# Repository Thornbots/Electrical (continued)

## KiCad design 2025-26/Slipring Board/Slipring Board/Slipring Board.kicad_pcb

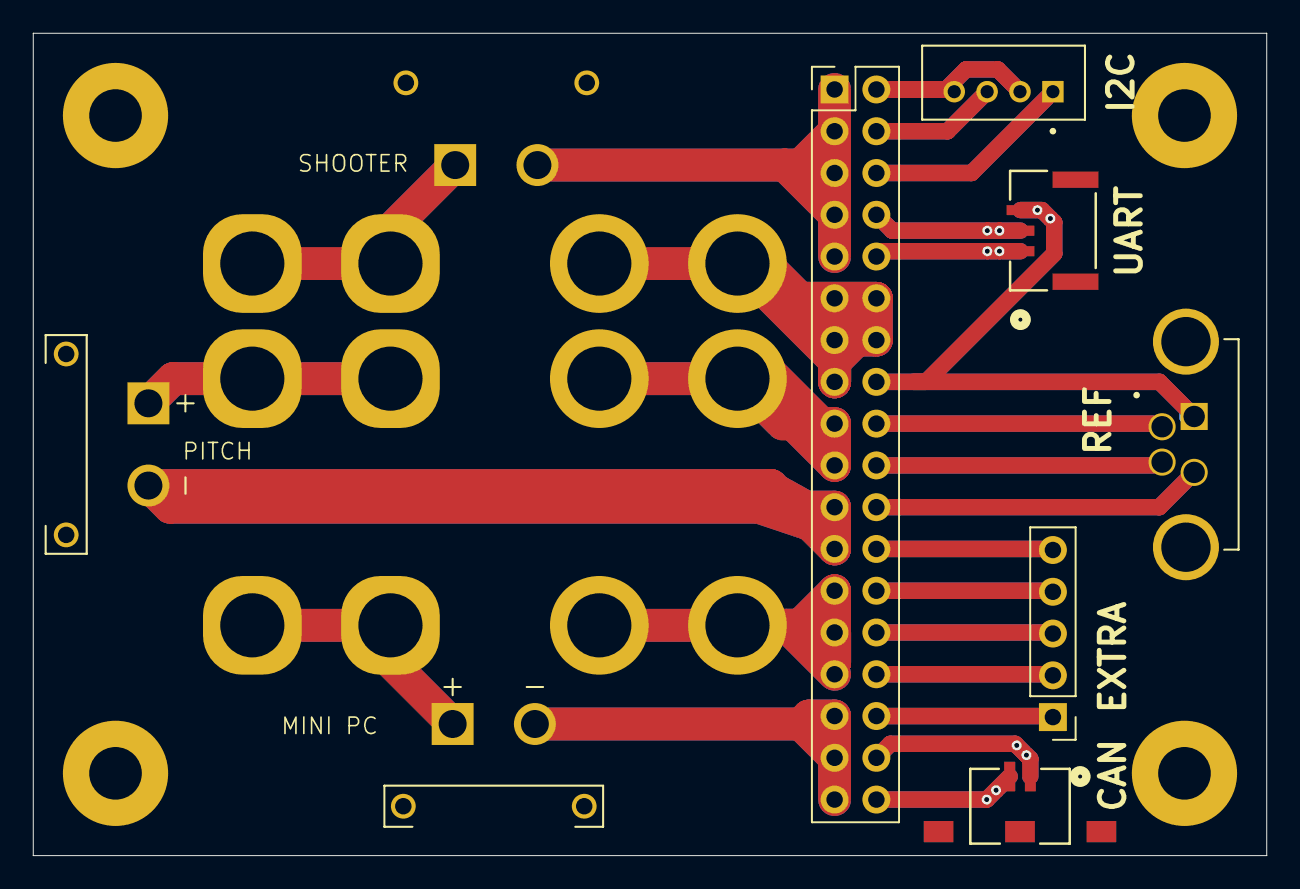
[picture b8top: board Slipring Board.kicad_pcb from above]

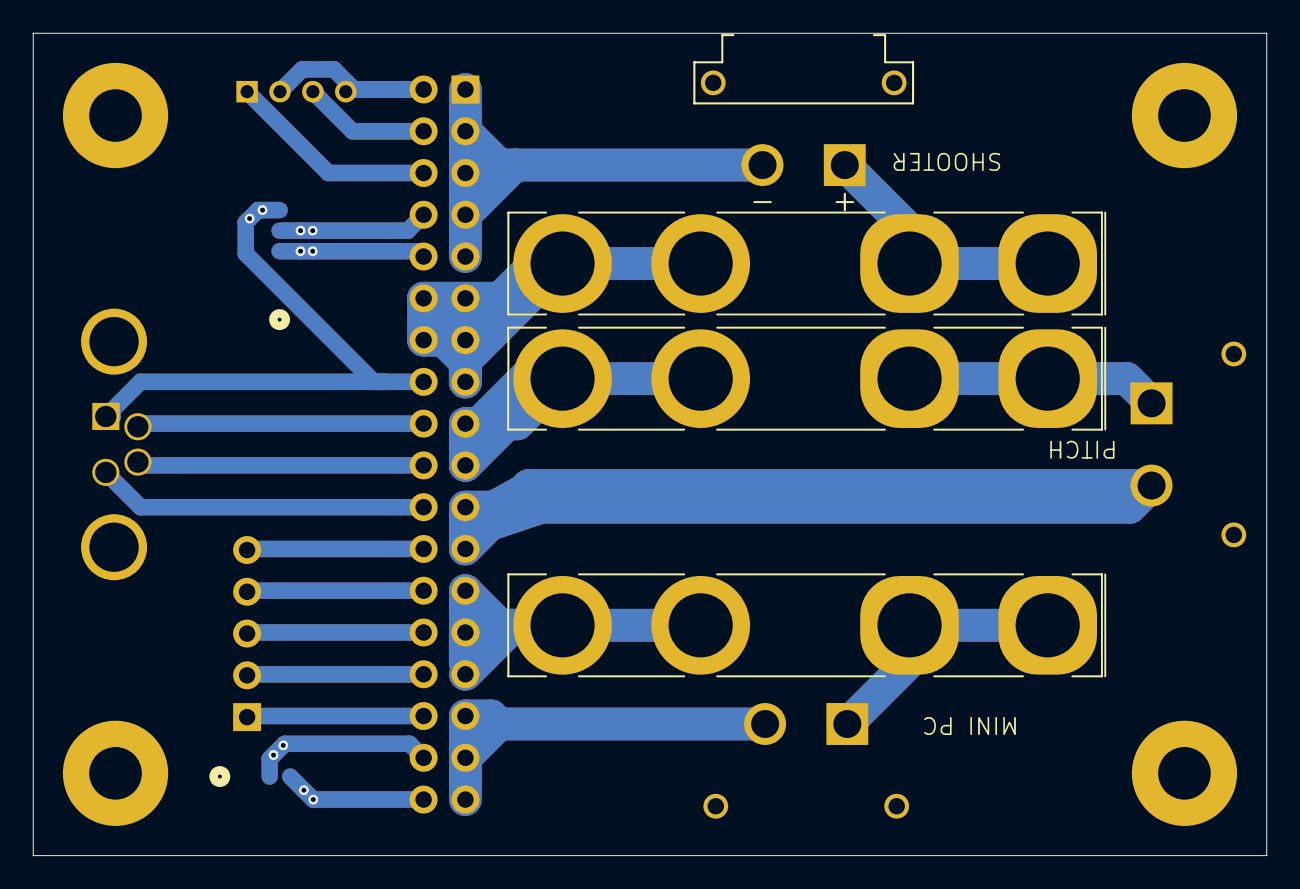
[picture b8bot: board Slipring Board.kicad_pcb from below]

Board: 2 copper layers, 75.0 x 50.0 mm, 12 parts (4 on the bottom side), 25 nets.

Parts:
F1, F2, F3: Fuse; Fuseholder_Keystone_3555-2
J1, J2, J3: Conn_01x02; AMASS_XT30PW-F
J4: JST GH 2pin; CONN_BM02B-GHS-TBT_JST
J5: M8 Aviator; AMPHENOL_M8S-04PFFR-SF8001
J6: JST GH 3pin; CONN_BM03B-GHS-TBT_JST
J7: JST PH 4pin; JST_B4B-PH-K
J8: Conn_02x18_Odd_Even; PinHeader_2x18_P2.54mm_Vertical
J9: Conn_01x05_Pin; PinHeader_1x05_P2.54mm_Vertical

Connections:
/CAN High: J4.2, J8.36
/CAN Low: J4.1, J8.34
/I2C Clock: J7.1, J8.6
/I2C Data: J7.3, J8.4
/I2C GND: J7.2, J7.4, J8.2
/Mini PC +24: F3.1, J3.1
/Mini PC GND: J3.2, J8.31, J8.33, J8.35
/Pitch +24: F2.1, J2.1
/Pitch GND: J2.2, J8.21, J8.23
/REF / UART GND: J5.1, J6.3, J8.16
/Ref +: J5.2, J8.18
/Ref Data A: J5.4, J8.20
/Ref Data B: J5.3, J8.22
/Shooter +24V: F1.1, J1.1
/Shooter GND: J1.2, J8.1, J8.3, J8.5, J8.7, J8.9
/UART 1 rx: J6.2, J8.8
/UART 1 tx: J6.1, J8.10
unnamed: F1.2, J8.11, J8.12, J8.13, J8.14, J8.15
unnamed: F2.2, J8.17, J8.19
unnamed: J8.24, J9.5
unnamed: F3.2, J8.25, J8.27, J8.29
unnamed: J8.26, J9.4
unnamed: J8.28, J9.3
unnamed: J8.30, J9.2
unnamed: J8.32, J9.1

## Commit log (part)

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2023-09-06 Create Lila Beghtel
2023-09-09 example project 1
2023-09-10 initial project commit
2023-09-10 power planes NOW
2023-09-10 project 1 mcdaniel
2023-09-10 project1
2023-09-10 Project 1 (Battershell_Luci)
2023-09-10 meeting 1
2023-09-10 groovy
2023-09-10 its not a bomb I promise
    its not a bomb I promise
2023-09-10 Practice
2023-09-10 bonillml-project-1
2023-09-10 prj1
2023-09-10 project2
2023-09-17 still not a bomb
2023-09-26 USBC Thingy
2023-09-26 aaaaa
2023-09-26 project 1
2023-09-26 power first push
2023-09-26 Boinkers (CAN)
2023-09-26 sd card reader first push
2023-09-26 Create RP2040
2023-09-26 new folder stuff
2023-09-30 found part
2023-10-01 rp2040 progress
2023-10-01 rp2040 update
2023-10-01 GPIO / UART
2023-10-01 2040 update
2023-10-01 done
2023-10-01 not important
2023-10-01 nothing important
2023-10-01 some power stuff variables
2023-10-01 I want to scream
2023-10-01 Added subschematic box
2023-10-01 fixed some minor wiring
2023-10-01 hmmm
2023-10-01 GPIO
2023-10-01 My Attempt at a CAN bus SPI bridge
2023-10-01 commented on evan's thing
2023-10-03 Fixed my schematic
2023-10-03 GPIO, USBC
2023-10-03 CAN booos
2023-10-07 power powered
2023-10-10 pushing origin
2023-10-10 fixed ben's whoopsie
2023-10-10 Fixed
2023-10-10 making heirachical sheet thing and switching docs
    changing to RP2040ACTUAL03 and 04 cuz it disappeared ?
2023-10-10 Changed Global to Hierarchals
2023-10-10 extra naming stuff
2023-10-10 We went thru eveeeryyything
2023-10-10 Idk what changed here
2023-10-10 GP1O to GPIO :|
2023-10-10 Found a symbol for the SD card reader
2023-10-10 Moved symbol to box
2023-10-10 Put SD Card Reader in box and added to pcb
2023-10-12 hi im electrical now
2023-10-13 RP2040 +Flash Drive
2023-10-17 Did Stuff
2023-10-17 BAn Cuss
2023-10-17 footprint stuff
2023-10-18 random commit and push
2023-10-22 board boarded
2023-10-22 Didn't do anything but it's making me anyway
2023-10-22 Team Meeting
    Dear Diary,
    today i had a thing
    it was a horrible thing
    a very horrible horrible thing
    i hated it
2023-10-23 My design for the power pcb
2023-10-27 Random Commit
2023-10-29 Board Design WIP
2023-10-29 Did some Redoing and added some footprints
2023-10-31 BOOTSEL
2023-10-31 Autosave shit?
2023-10-31 Branch
2023-10-31 Bootsel stuff
2023-10-31 SD Card Stuff
2023-11-05 Footprint Assignments
    Assigned footprints to things that didn't currently have ones
2023-11-05 bootsel
    just connected to data
2023-11-05 Meeting Stuff
2023-11-06 dual rp2040z
2023-11-08 Schematics
2023-11-21 v1 functionality finished
2023-11-26 schematic finished, placement progress
2023-11-27 first pass placement doone
2023-11-29 Yippee
2023-12-03 Adjusted Caps for RP2040
    So we don't have as many capacitors that we don't need
2023-12-03 Document-Updated Version
    Used the Pico Doc to update the Power, Flash, and BootSel schematics.
2023-12-03 ADDED 1V1 TO RP2040
2023-12-06 PUshing before Matt Does
2023-12-10 LED Array
2023-12-10 It's Long Now
2023-12-10 Rose Pilk - Now Pilkier
2023-12-13 Big changes
2023-12-13 Completed Picos?
2023-12-14 I changed things shit my bad
2023-12-14 changez
2023-12-15 TRACING PLACING AND OTHER SHIT I CAN'T BE BOTHERED DESCRIBING
2023-12-15 Post Mark Crosby
2024-01-10 Tracing part 2
2024-01-10 tweaks
2024-01-10 redid some of the traces
2024-01-26 Retracing
2024-01-28 cleaned up a tid
2024-01-30 twkz
2024-02-01 ahhhhh
2024-02-01 power hour
2024-02-02 gerbz
2024-02-04 fuck
2024-02-06 moved board
2024-02-09 did more shit
2024-02-10 Did you check Autoroute Pass 15
2024-02-11 sigh
2024-07-10 Making the Repo Look better
    Hopefully this will make it more.. coherent
2024-07-10 First Push for Armor Panel
2024-07-10 Second Armor Panel Push
2024-07-12 Bug Fixes
2024-07-14 Push
    I push so i can close github w/o feeling bad
2024-09-22 Idk why but yeah
2024-09-22 First Push of the Year LOL
2024-09-22 Erm what the
2024-09-22 Yay I have a folder
2024-09-22 Relearned KiCAD
2024-09-23 Onboarding
2024-09-23 Added Self-Folder
2024-09-23 FEET
2024-09-23 Just wanna pull
2024-09-23 added library
2024-09-23 bruh
2024-09-23 Test
2024-09-23 Finished schematic
2024-09-29 yea
    pushing stuff i did the past 2 meetings
2024-09-29 Created a folder
2024-09-29 Fixing my Mistakes part infinity
2024-09-29 There_You_Go
2024-10-08 Put together Board maybe?
2024-11-04 mandatory push
2024-11-04 pushign moemnet
2024-11-04 Nothing
2024-11-04 I'm Lovin It
2024-11-05 trollface board
    adds my trollface board to the silly boards
2025-01-14 gyat daym
2025-09-18 Gitignore and added 2526 teaching stuff
2025-09-19 my first pcb :)))
    wohooo
2025-09-19 KiCAD practice waow
    q(≧▽≦q)
2025-09-19 Designed Example Board
2025-09-19 Designed my first board :)
2025-09-19 I designed a really cool board!!11!! SO COOL!!!1
    <o>
2025-09-21 Added Board and mounting spots for armor panel
2025-09-21 Schematic
2025-09-21 power boost board footprint
    yeah
2025-09-21 wire THT pad footprint
    yeahhh
2025-09-21 Forgot to connect pads
2025-09-21 Added new switch for improved armor plating
2025-09-26 My Armor Panel
2025-09-26 Updated Armor Panel Switch
2025-09-26 my board (○｀ 3′○)
    made a armor panel board...just some scribbles ＞﹏＜
2025-09-28 Fixed Connectors
2025-09-28 Fixed Stuff
2025-09-28 My epic cool board
2025-09-28 faux armor panel
    my power boost board is sideways
2025-09-28 i think i finished my board yippeee ( •̀ ω •́ )✧
    finished my board for the armor panel yahoo
2025-10-05 Finished board design
2025-10-05 Finalized Armor Panel
2025-10-05 Updated board with Gerber files
2025-10-19 Unholy Abomination
2025-10-19 updated
    everything is a connector
2025-10-19 Updated Armor Panel (10/19/2025)
    Major revision (no more switches)
2025-10-24 slipring board
    just the bus
2025-11-02 Added XT30 footprints
2025-11-02 More footprints
2025-11-02 One more footprint
2025-11-02 Another one
2025-11-09 connectors
    unwired tho
2025-11-14 Created slipring footprint folder
2025-11-14 Made several footprint and schematic updates
2025-11-15 Fixed the madness
2025-11-16 added fuses, fixed 2x18 size, added edgecuts
2025-11-26 first rev of slipring board
2025-12-04 widened traces
2025-12-05 gerber
2026-01-18 Started Measurement Board (To be finished later)
2026-01-21 Still working
2026-01-22 Finished basic schematic
2026-01-30 Changed the block
2026-01-30 Updating PSU
    Updated the 5V PSU Schematic with the correct components
2026-02-01 beautified schematic a little bit
    yeah
2026-02-01 Some board thingy
2026-02-02 fixed all footprints
    also added the pad areas for the alligator clips
2026-02-05 made pcb design
    made a pcb design for the measurement board idk if its good we will go over it during meeting today i think. woaw :3
2026-02-05 fixed schem issues, reset my board bc it did not have a gnd plane
    yahooooooooooo
    fixed the labels to be global, fixed a missing ground on schem.
    added a ground plane to the board, removed traces (to redo with the ground plane)
    - Rowan :3
2026-02-07 Lets do this one more time....
    Redid supercap measurement ICs testing board PCB. Couldn't quite get 50x50mm. Tried to keep traces as big and short as possible but some are longer/thinner than ideal. will PCB review sunday (2/8)?
    ><> ><> ><> ><> ><>
2026-02-08 started adding vias but then i realized idk what im doing
2026-02-08 basic layout done
    yeah
2026-02-08 mwahawhwhahwa i took over the branch and wired things up and also added miku the pcb should be finsisedh now maybe it can be checked woawawo
2026-02-15 addes second adc, compacted board, and redid traces
    yippee
2026-02-25 trying to panelize before ordering
    i have no clue what kikit does
2026-03-23 a lot has been done
    i dont even remember
2026-03-24 Started Schematic for Control Board
    I misnamed it i thought it was V3 but theres no V2 :(
2026-04-04 Measurement Testing Code
    trying to implement SPI on the pico and read channel 2 (potentiometer)
2026-04-05 fixed ADC reading
    something something claude big endian idrk
2026-05-12 board almost fully designed
    i want to try a different orientation so gonna push this so i can easily revert
